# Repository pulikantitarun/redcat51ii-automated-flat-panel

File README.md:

# Universal automated telescope flat panel — Rev C

Rev C is a single-board automated flat-field panel and motorized dust cover. The
included mechanical preset fits the RedCat 51 II, while the parametric CAD supports
other telescope/dew-shield diameters without changing the electronics.

Control options:

- **ASIAIR Plus:** isolated adjustable-output input on J2.
- **ASCOM:** USB-C to the included ASCOM Alpaca CoverCalibrator bridge.
- **Manual:** long-press the onboard or external button.

ASCOM commands receive a renewable 15-second control lease. If the USB bridge stops,
the controller automatically returns to ASIAIR control. USB-C can power the logic for
safe firmware loading, but MAIN 12 V is required for the servo and light panel.

## Rev C improvements

- valid, separately fused input, LED, and servo branches;
- MCU-switched servo rail that defaults off;
- keyed JST-XH servo connector;
- fail-safe normally-closed limit wiring with RC filtering and ESD protection;
- 12 V presence sensing and USB/12 V logic-power ORing;
- native USB-C programming and ASCOM data;
- test pads and UART recovery header;
- filtered ASIAIR input, command hysteresis, 400 ms stability requirement;
- debounced limits, ramped motion, move timeout, fault reporting, NVS calibration;
- LED warm-up/ramp and brightness gamma setting;
- adjustable-diameter CAD, fit gauge, hard-stop tabs, tether eyes, strain relief,
  gasket channel, and Customizer-friendly OpenSCAD clamp.

## Manufacturing set

For turnkey PCB assembly upload:

1. `pcb/Gerbers_RevC.zip`
2. `pcb/BOM.csv`
3. `pcb/PickAndPlace.csv`

Attach `pcb/PCB_Assembly_Top.pdf` and state that both SMT and through-hole parts are
to be assembled. Recommended board order:

- 120 x 75 mm, 4 layers, 1.6 mm FR-4;
- 2 oz finished copper on all layers;
- ENIG, lead-free assembly;
- green solder mask and white silkscreen;
- electrical test, AOI, and assembly inspection photographs;
- turnkey sourcing with no substitutions for U1, U3, U4, L1, L2, Q1/Q3, F1-F3,
  C2, or C7 without approval.

The routed board passes KiCad error-level DRC with **0 errors and 0 unconnected pads**.
All eight supplied STLs are watertight. Silkscreen-only warnings from edge-mounted
connector footprints are recorded separately and do not affect copper fabrication.

## Default RedCat preset

The included STLs use:

- measured scope/dew-shield OD: 80.0 mm;
- 0.8 mm liner per side;
- 0.5 mm diametral print clearance;
- resulting clamp bore: 82.1 mm;
- optical stack diameter: 82 mm.

Do not assume your telescope matches that measurement. Print the short fit gauge
first. See `mechanical/PRESETS.md` for other diameters.

An additional ready-generated **Askar 103 APO starting preset** is included in
`mechanical/presets/Askar-103-APO`. It uses the published 122 mm dew-shield OD,
a 124.1 mm lined clamp bore, and a 125 mm illuminated stack. Measure the actual
shield and print its fit gauge before using the full clamp.

## Release map

- `pcb/` — Gerbers, BOM, centroid, DRC, PDFs, 3D render, STEP, and KiCad source.
- `mechanical/` — STL/STEP parts, CadQuery generator, and OpenSCAD Customizer source.
- `firmware/` — compiled 8 MB ESP32-S3 image and source sketch.
- `ascom/` — tested Windows Alpaca bridge executable and source.
- `docs/INSTALLATION.md` — universal physical installation and wiring.
- `docs/CIRCUIT.md` — circuit blocks, connector map, and GPIO allocation.
- `docs/CONTROL.md` — ASIAIR, ASCOM, manual operation, and USB command protocol.
- `docs/FIRST_ARTICLE_TEST.md` — mandatory electrical, thermal, and optical checks.
- `docs/PCB_ASSEMBLY_ORDER.md` — manufacturer form values and assembly notes.

## Safety and release status

This is a fabrication-ready open-hardware prototype, not a physically qualified
commercial product. DRC, firmware compilation, ASCOM management API, and mesh integrity
were verified digitally. A real first article must still pass the supplied power,
servo-stall, thermal, ASIAIR-output, full-mount-clearance, and illumination-uniformity
tests before unattended use. Always fit the secondary tether.

## License

Hardware, CAD, firmware, bridge software, and documentation are released under
the GNU General Public License v3.0. See `LICENSE` for the full license text.

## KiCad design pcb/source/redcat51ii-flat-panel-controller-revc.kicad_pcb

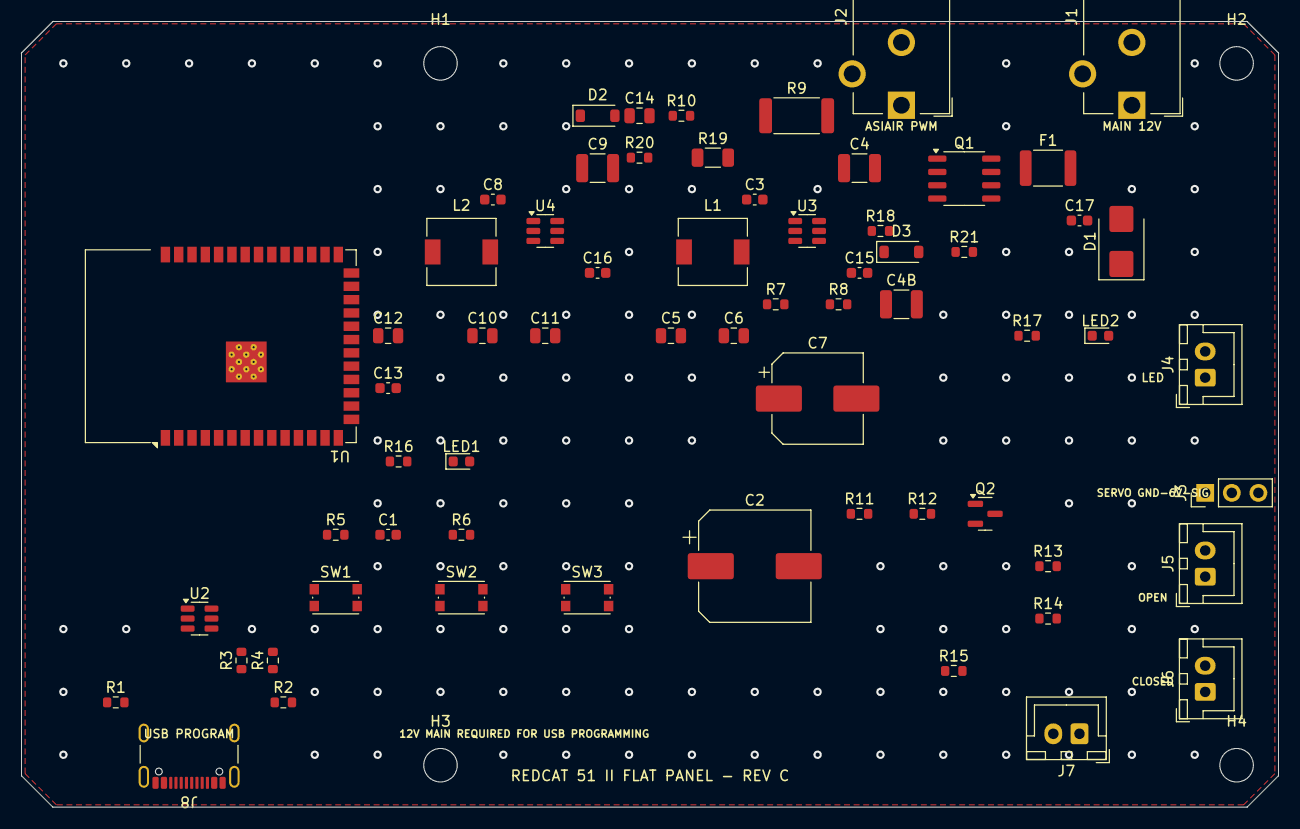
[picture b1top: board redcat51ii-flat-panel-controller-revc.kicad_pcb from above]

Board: 4 copper layers, 120.0 x 75.0 mm, 68 parts (0 on the bottom side), 35 nets, no tracks yet.

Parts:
C1: 1uF; C_0603_1608Metric
C2: 470uF 25V; CP_Elec_10x10.5
C3, C8, C13, C15, C16, C17: 100nF; C_0603_1608Metric
C4, C4B, C9: 10uF 25V; C_1210_3225Metric
C5, C6, C10, C11: 22uF 10V; C_0805_2012Metric
C7: 470uF 10V; CP_Elec_8x10.5
C12, C14: 10uF; C_0805_2012Metric
D1: SMBJ14A; D_SMB
D2: MMSZ5226B 3V3; D_SOD-123
D3: MMSZ5240B 10V; D_SOD-123
F1: 4A 16V PTC; Fuse_1812_4532Metric
H1, H2, H3, H4: M3; MountingHole_3.2mm_M3
J1: MAIN 12V DC5521; BarrelJack_CUI_PJ-102AH_Horizontal
J2: ASIAIR PWM DC5521; BarrelJack_CUI_PJ-102AH_Horizontal
J3: SERVO GND 6V SIG; PinHeader_1x03_P2.54mm_Vertical
J4: LED PANEL; JST_XH_B2B-XH-A_1x02_P2.50mm_Vertical
J5: OPEN LIMIT; JST_XH_B2B-XH-A_1x02_P2.50mm_Vertical
J6: CLOSED LIMIT; JST_XH_B2B-XH-A_1x02_P2.50mm_Vertical
J7: EXT MANUAL; JST_XH_B2B-XH-A_1x02_P2.50mm_Vertical
J8: USB-C PROGRAM; USB_C_Receptacle_GCT_USB4105-xx-A_16P_TopMnt_Horizontal
L1: 3.3uH 6.5A; L_6.3x6.3_H3
L2: 4.7uH 3A; L_6.3x6.3_H3
LED1: STATUS BLUE; LED_0603_1608Metric
LED2: POWER GREEN; LED_0603_1608Metric
Q1: AO4407A; SO-8_3.9x4.9mm_P1.27mm
Q2: AO3400A; SOT-23
R1, R2: 5.1k; R_0603_1608Metric
R3, R4: 22R; R_0603_1608Metric
R5, R6, R10, R12, R13, R14, R15: 10k; R_0603_1608Metric
R7: 64.9k 1%; R_0603_1608Metric
R8: 10k 1%; R_0603_1608Metric
R9: 470R 1W; R_2512_6332Metric
R11: 100R; R_0603_1608Metric
R16, R17: 1k; R_0603_1608Metric
R18, R21: 100k; R_0603_1608Metric
R19: 0R; R_1206_3216Metric
R20: 3k3; R_0603_1608Metric
SW1: RESET; SW_Push_1P1T_NO_CK_KMR2
SW2: BOOT; SW_Push_1P1T_NO_CK_KMR2
SW3: MANUAL; SW_Push_1P1T_NO_CK_KMR2
U1: ESP32-S3-WROOM-1-N8R8; ESP32-S3-WROOM-1
U2: USBLC6-2SC6; SOT-23-6
U3: AP62401WU-7; TSOT-23-6
U4: AP63203WU-7; TSOT-23-6

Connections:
+3V3: C10.1, C11.1, C12.1, C13.1, L2.2, R5.1, R6.1, R13.1, R14.1, R15.1, R17.1, U1.2, U4.4
+6V: C5.1, C6.1, C7.1, J3.2, L1.2, R7.1
+12V: C2.1, C4.1, C4B.1, C9.1, C15.1, C16.1, D1.1, D3.1, J4.1, Q1.1, Q1.2, Q1.3, R18.1, U3.3, U4.3, U4.5
+12V_FUSED: F1.2, Q1.5, Q1.6, Q1.7, Q1.8
+12V_RAW: C17.1, F1.1, J1.1
ASIAIR+: J2.1, R9.1, R10.1
ASIAIR-: J2.2, J2.3, R9.2, R19.1
ASIAIR_SIG: C14.1, D2.1, R10.2, R20.1, U1.4
BOOT: R6.2, SW2.1, U1.27
BST3: C8.1, U4.6
BST6: C3.1, U3.6
BUTTON_SIG: J7.1, R15.2, SW3.1, U1.17
CC1: J8.A5, R1.1
CC2: J8.B5, R2.1
CLOSED_SIG: J6.1, R14.2, U1.7
EN: C1.1, R5.2, SW1.1, U1.3
EN6: R18.2, U3.5
FB6: R7.2, R8.1, U3.4
GATE12: D3.2, Q1.4, R21.1
GND: C1.2, C2.2, C4.2, C4B.2, C5.2, C6.2, C7.2, C9.2, C10.2, C11.2, C12.2, C13.2, C14.2, C15.2, C16.2, C17.2, D1.2, D2.2, J1.2, J1.3, J3.1, J5.2, J6.2, J7.2, J8.A1, J8.A12, J8.B1, J8.B12, J8.S1, LED1.1, LED2.1, Q2.2, R1.2, R2.2, R8.2, R12.2, R19.2, R20.2, R21.2, SW1.2, SW2.2, SW3.2, U1.1, U1.40, U1.41, U2.2, U3.1, U4.1
LED_GATE: Q2.1, R11.2, R12.1
LED_NEG: J4.2, Q2.3
LED_PWM: R11.1, U1.5
OPEN_SIG: J5.1, R13.2, U1.6
PWR_LED: LED2.2, R17.2
SERVO_SIG: J3.3, U1.11
STATUS_A: LED1.2, R16.2
STATUS_LED: R16.1, U1.8
SW3: C8.2, L2.1, U4.2
SW6: C3.2, L1.1, U3.2
USB_D+: R3.2, U1.14
USB_D+_J: J8.A6, J8.B6, R3.1, U2.1, U2.6
USB_D-: R4.2, U1.13
USB_D-_J: J8.A7, J8.B7, R4.1, U2.3, U2.4
USB_VBUS: J8.A4, J8.A9, J8.B4, J8.B9, U2.5

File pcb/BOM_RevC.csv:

Comment,Designator,Footprint,Quantity
1uF,C1,C_0603_1608Metric,1
470uF 25V,C2,CP_Elec_10x10.5,1
100nF,"C3,C8,C13,C15,C16,C17",C_0603_1608Metric,6
10uF 25V,"C4B,C4,C9",C_1210_3225Metric,3
22uF 10V,"C5,C6,C10,C11",C_0805_2012Metric,4
470uF 10V,C7,CP_Elec_8x10.5,1
10uF,"C12,C14",C_0805_2012Metric,2
SMBJ14A,D1,D_SMB,1
MMSZ5226B 3V3,D2,D_SOD-123,1
MMSZ5240B 10V,D3,D_SOD-123,1
4A 16V PTC,F1,Fuse_1812_4532Metric,1
MAIN 12V DC5521,J1,BarrelJack_CUI_PJ-102AH_Horizontal,1
ASIAIR PWM DC5521,J2,BarrelJack_CUI_PJ-102AH_Horizontal,1
SERVO GND 6V SIG,J3,PinHeader_1x03_P2.54mm_Vertical,1
LED PANEL,J4,JST_XH_B2B-XH-A_1x02_P2.50mm_Vertical,1
OPEN LIMIT,J5,JST_XH_B2B-XH-A_1x02_P2.50mm_Vertical,1
CLOSED LIMIT,J6,JST_XH_B2B-XH-A_1x02_P2.50mm_Vertical,1
EXT MANUAL,J7,JST_XH_B2B-XH-A_1x02_P2.50mm_Vertical,1
USB-C PROGRAM,J8,USB_C_Receptacle_GCT_USB4105-xx-A_16P_TopMnt_Horizontal,1
3.3uH 6.5A,L1,L_6.3x6.3_H3,1
4.7uH 3A,L2,L_6.3x6.3_H3,1
STATUS BLUE,LED1,LED_0603_1608Metric,1
POWER GREEN,LED2,LED_0603_1608Metric,1
AO4407A,Q1,SO-8_3.9x4.9mm_P1.27mm,1
AO3400A,Q2,SOT-23,1
5.1k,"R1,R2",R_0603_1608Metric,2
22R,"R3,R4",R_0603_1608Metric,2
10k,"R5,R6,R10,R12,R13,R14,R15",R_0603_1608Metric,7
64.9k 1%,R7,R_0603_1608Metric,1
10k 1%,R8,R_0603_1608Metric,1
470R 1W,R9,R_2512_6332Metric,1
100R,R11,R_0603_1608Metric,1
1k,"R16,R17",R_0603_1608Metric,2
100k,"R18,R21",R_0603_1608Metric,2
0R,R19,R_1206_3216Metric,1
3k3,R20,R_0603_1608Metric,1
RESET,SW1,SW_Push_1P1T_NO_CK_KMR2,1
BOOT,SW2,SW_Push_1P1T_NO_CK_KMR2,1
MANUAL,SW3,SW_Push_1P1T_NO_CK_KMR2,1
ESP32-S3-WROOM-1-N8R8,U1,ESP32-S3-WROOM-1,1
USBLC6-2SC6,U2,SOT-23-6,1
AP62401WU-7,U3,TSOT-23-6,1
AP63203WU-7,U4,TSOT-23-6,1

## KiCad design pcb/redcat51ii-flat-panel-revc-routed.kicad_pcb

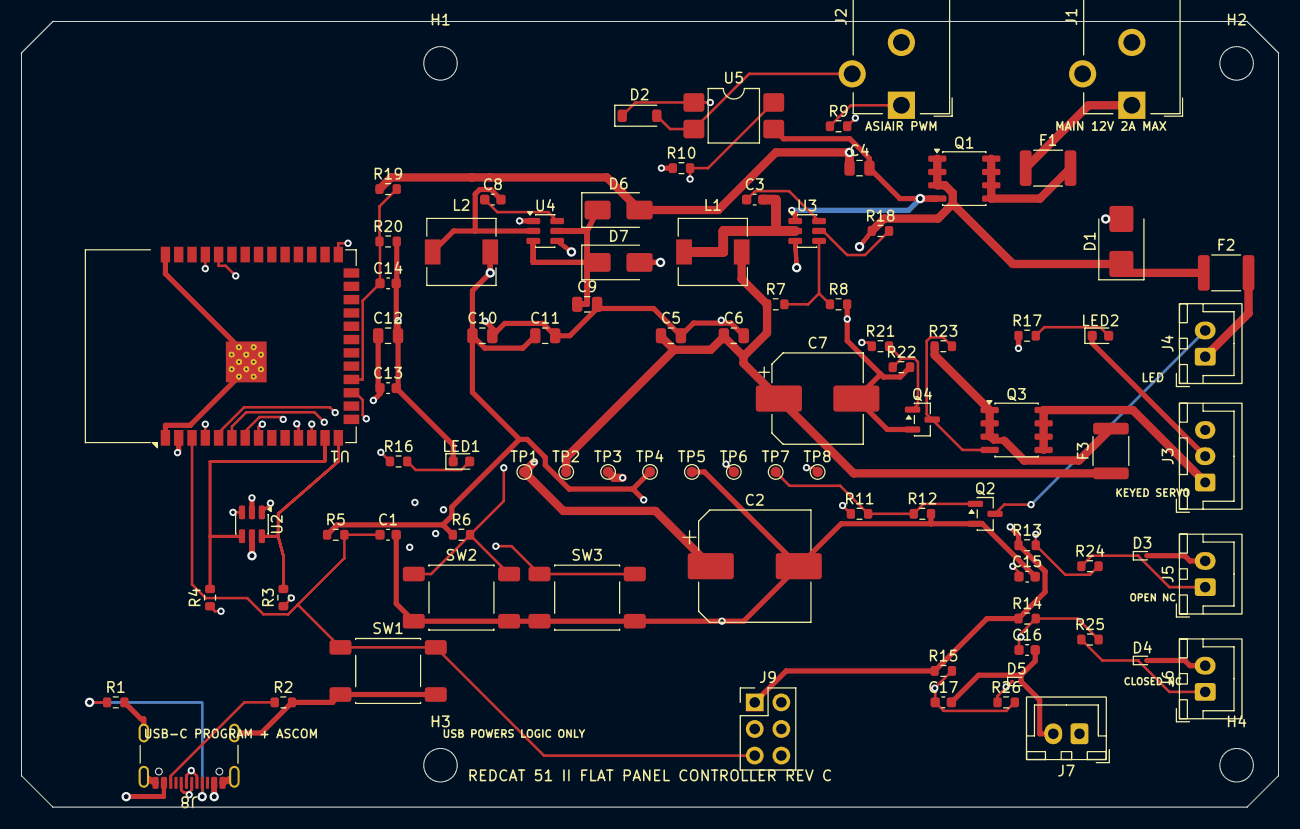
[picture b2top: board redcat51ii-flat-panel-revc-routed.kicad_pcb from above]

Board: 4 copper layers, 120.0 x 75.0 mm, 90 parts (0 on the bottom side), 48 nets.

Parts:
C1: 1uF; C_0603_1608Metric
C2: 470uF 25V; CP_Elec_10x10.5
C3, C8, C13, C14, C15, C16, C17: 100nF; C_0603_1608Metric
C4, C9: 10uF 25V; C_0805_2012Metric
C5, C6, C10, C11: 22uF 10V; C_0805_2012Metric
C7: 470uF 10V; CP_Elec_8x10.5
C12: 10uF; C_0805_2012Metric
D1: SMBJ18A; D_SMB
D2: 1N4148W; D_SOD-123
D3, D4, D5: ESD9B3.3ST5G; D_SOD-923
D6: SS14 12V LOGIC OR; D_SMA
D7: SS14 USB LOGIC OR; D_SMA
F1: MF-MSMF200/16X 2A 16V PTC; Fuse_1812_4532Metric
F2: MF-MSMF110/16X LED 1.1A; Fuse_1812_4532Metric
F3: MF-MSMF260/8X SERVO 2.6A; Fuse_1812_4532Metric
H1, H2, H3, H4: M3; MountingHole_3.2mm_M3
J1: MAIN 12V DC5521; BarrelJack_CUI_PJ-102AH_Horizontal
J2: ASIAIR PWM DC5521; BarrelJack_CUI_PJ-102AH_Horizontal
J3: KEYED SERVO 6V GND SIG; JST_XH_B3B-XH-A_1x03_P2.50mm_Vertical
J4: LED PANEL; JST_XH_B2B-XH-A_1x02_P2.50mm_Vertical
J5: OPEN LIMIT NC; JST_XH_B2B-XH-A_1x02_P2.50mm_Vertical
J6: CLOSED LIMIT NC; JST_XH_B2B-XH-A_1x02_P2.50mm_Vertical
J7: EXT MANUAL; JST_XH_B2B-XH-A_1x02_P2.50mm_Vertical
J8: USB-C PROGRAM; USB_C_Receptacle_GCT_USB4105-xx-A_16P_TopMnt_Horizontal
J9: UART RECOVERY; PinHeader_2x03_P2.54mm_Vertical
L1: 3.3uH 6.5A; L_6.3x6.3_H3
L2: 4.7uH 3A; L_6.3x6.3_H3
LED1: STATUS BLUE; LED_0603_1608Metric
LED2: POWER GREEN; LED_0603_1608Metric
Q1: AO4407A; SO-8_3.9x4.9mm_P1.27mm
Q2: AO3400A; SOT-23
Q3: AO4407A SERVO SWITCH; SO-8_3.9x4.9mm_P1.27mm
Q4: MMBT3904; SOT-23
R1, R2: 5.1k; R_0603_1608Metric
R3, R4: 22R; R_0603_1608Metric
R5, R6, R10, R12, R13, R14, R15: 10k; R_0603_1608Metric
R7: 64.9k 1%; R_0603_1608Metric
R8: 10k 1%; R_0603_1608Metric
R9: 2.2k; R_0603_1608Metric
R11: 100R; R_0603_1608Metric
R16, R17, R24, R25, R26: 1k; R_0603_1608Metric
R18, R19, R22, R23: 100k; R_0603_1608Metric
R20: 22k; R_0603_1608Metric
R21: 4.7k; R_0603_1608Metric
SW1: RESET; SW_Push_1P1T_NO_E-Switch_TL3301NxxxxxG
SW2: BOOT; SW_Push_1P1T_NO_E-Switch_TL3301NxxxxxG
SW3: MANUAL; SW_Push_1P1T_NO_E-Switch_TL3301NxxxxxG
TP1: 12V; TestPoint_Pad_D1.0mm
TP2: 6V; TestPoint_Pad_D1.0mm
TP3: 6V_SW; TestPoint_Pad_D1.0mm
TP4: 3V3; TestPoint_Pad_D1.0mm
TP5: GND; TestPoint_Pad_D1.0mm
TP6: ASIAIR; TestPoint_Pad_D1.0mm
TP7: LED_GATE; TestPoint_Pad_D1.0mm
TP8: SERVO_SIG; TestPoint_Pad_D1.0mm
U1: ESP32-S3-WROOM-1-N8; ESP32-S3-WROOM-1
U2: USBLC6-2SC6; SOT-23-6
U3: AP62401WU-7; TSOT-23-6
U4: AP63203WU-7; TSOT-23-6
U5: LTV-817S; SMDIP-4_W7.62mm

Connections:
+3V3: C10.1, C11.1, C12.1, C13.1, J9.1, L2.2, R5.1, R6.1, R10.1, R13.1, R14.1, R15.1, R17.1, TP4.1, U1.2, U4.4
+6V: C5.1, C6.1, C7.1, F3.1, L1.2, R7.1, TP2.1
+6V_FUSED: F3.2, Q3.1, Q3.2, Q3.3, R23.1
+6V_SERVO: J3.1, Q3.5, Q3.6, Q3.7, Q3.8, TP3.1
+12V: C2.1, C4.1, D1.1, D6.2, F2.1, Q1.1, Q1.2, Q1.3, R18.1, R19.1, TP1.1, U3.3
+12V_FUSED: F1.2, Q1.5, Q1.6, Q1.7, Q1.8
+12V_LED: F2.2, J4.1
+12V_RAW: F1.1, J1.1
ASIAIR+: J2.1, R9.1
ASIAIR-: D2.2, J2.2, J2.3, U5.2
ASIAIR_LED: D2.1, R9.2, U5.1
ASIAIR_SIG: R10.2, TP6.1, U1.4, U5.4
BOOT: J9.6, R6.2, SW2.1, U1.27
BST3: C8.1, U4.6
BST6: C3.1, U3.6
BUTTON_RAW: D5.1, J7.1, R26.1
BUTTON_SIG: C17.1, R15.2, R26.2, SW3.1, U1.17
CC1: J8.A5, R1.1
CC2: J8.B5, R2.1
CLOSED_RAW: D4.1, J6.1, R25.1
CLOSED_SIG: C16.1, R14.2, R25.2, U1.7
EN: C1.1, J9.5, R5.2, SW1.1, U1.3
EN6: R18.2, U3.5
FB6: R7.2, R8.1, U3.4
GND: C1.2, C2.2, C4.2, C5.2, C6.2, C7.2, C9.2, C10.2, C11.2, C12.2, C13.2, C14.2, C15.2, C16.2, C17.2, D1.2, D3.2, D4.2, D5.2, J1.2, J1.3, J3.2, J5.2, J6.2, J7.2, J8.A1, J8.A12, J8.B1, J8.B12, J8.SH, J9.2, LED1.1, LED2.1, Q1.4, Q2.2, Q4.2, R1.2, R2.2, R8.2, R12.2, R20.2, R22.2, SW1.2, SW2.2, SW3.2, TP5.1, U1.1, U1.40, U1.41, U2.2, U3.1, U4.1, U5.3
LED_GATE: Q2.1, R11.2, R12.1, TP7.1
LED_NEG: J4.2, Q2.3
LED_PWM: R11.1, U1.5
LOGIC_VIN: C9.1, D6.1, D7.1, U4.3, U4.5
OPEN_RAW: D3.1, J5.1, R24.1
OPEN_SIG: C15.1, R13.2, R24.2, U1.6
PWR_LED: LED2.2, R17.2
PWR_SENSE: C14.1, R19.2, R20.1, U1.18
SERVO_BASE: Q4.1, R21.2, R22.1
SERVO_GATE: Q3.4, Q4.3, R23.2
SERVO_PWR_EN: R21.1, U1.12
SERVO_SIG: J3.3, TP8.1, U1.11
STATUS_A: LED1.2, R16.2
STATUS_LED: R16.1, U1.8
SW3: C8.2, L2.1, U4.2
SW6: C3.2, L1.1, U3.2
UART_RX: J9.4, U1.36
UART_TX: J9.3, U1.37
USB_D+: R3.2, U1.14, U2.6
USB_D+_J: J8.A6, J8.B6, R3.1, U2.1
USB_D-: R4.2, U1.13, U2.4
USB_D-_J: J8.A7, J8.B7, R4.1, U2.3
USB_VBUS: D7.2, J8.A4, J8.A9, J8.B4, J8.B9, U2.5

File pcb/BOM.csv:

Item,Designator,Qty,Manufacturer,Manufacturer Part Number,Description,Package,Assembly Notes
1,U1,1,Espressif,ESP32-S3-WROOM-1-N8,ESP32-S3 module 8MB flash,ESP32-S3-WROOM-1,Antenna end at board edge; no PSRAM required
2,U2,1,STMicroelectronics,USBLC6-2SC6,USB 2-line ESD protector,SOT-23-6,
3,U3,1,Diodes Incorporated,AP62401WU-7,4A forced-PWM synchronous buck,TSOT-23-6,
4,U4,1,Diodes Incorporated,AP63203WU-7,3.3V 2A synchronous buck,TSOT-23-6,
5,U5,1,Lite-On,LTV-817S-TA1,Optocoupler,SMDIP-4 W7.62,
6,Q1 Q3,2,Alpha & Omega Semiconductor,AO4407A,P-channel MOSFET reverse protection / servo switch,SO-8,
7,Q2,1,Alpha & Omega Semiconductor,AO3400A,N-channel LED MOSFET,SOT-23,
8,Q4,1,onsemi,MMBT3904LT1G,NPN servo-gate driver,SOT-23,
9,D1,1,Littelfuse,SMBJ18A,18V unidirectional TVS diode,SMB,Observe cathode mark
10,D2,1,Diodes Incorporated,1N4148W-7-F,Optocoupler reverse clamp,SOD-123,Observe cathode mark
11,D3 D4 D5,3,onsemi,ESD9B3.3ST5G,3.3V bidirectional ESD protection,SOD-923,
12,D6 D7,2,Diodes Incorporated,SS14-13-F,1A 40V Schottky power OR diode,SMA,Observe cathode mark
13,F1,1,Bourns,MF-MSMF200/16X-2,2.0A hold 16V resettable input fuse,1812,System continuous input rating is 2A
14,F2,1,Bourns,MF-MSMF110/16X-2,1.1A hold 16V resettable LED fuse,1812,
15,F3,1,Bourns,MF-MSMF260/8X-2,2.6A hold 8V resettable servo fuse,1812,
16,L1,1,Coilcraft,XAL6060-332MEB,3.3uH shielded inductor 6.5A,6x6mm,
17,L2,1,Bourns,SRN6045TA-4R7M,4.7uH shielded inductor,6x6mm,Confirm pad compatibility during DFM
18,C2,1,Panasonic,EEE-FK1E471P,470uF 25V low-ESR capacitor,10x10.2mm,Observe polarity
19,C7,1,Panasonic,EEE-FK1A471P,470uF 10V low-ESR capacitor,8x10.2mm,Observe polarity
20,C4 C9,2,Murata,GRM21BR61E106KA73L,10uF 25V X5R,0805,
21,C5 C6 C10 C11,4,Murata,GRM21BR61A226ME44L,22uF 10V X5R,0805,
22,C12,1,Murata,GRM21BR61A106KE19L,10uF 10V X5R,0805,
23,C1,1,Murata,GRM188R61A105KA61D,1uF 10V X5R,0603,
24,C3 C8 C13 C14 C15 C16 C17,7,Murata,GRM188R71C104KA01D,100nF 16V X7R,0603,
25,R1 R2,2,Yageo,RC0603FR-075K1L,5.1k 1%,0603,
26,R3 R4,2,Yageo,RC0603FR-0722RL,22R 1%,0603,
27,R5 R6 R8 R10 R12 R13 R14 R15,8,Yageo,RC0603FR-0710KL,10k 1%,0603,
28,R7,1,Yageo,RC0603FR-0764K9L,64.9k 1%,0603,
29,R9,1,Yageo,RC0603FR-072K2L,2.2k 1%,0603,
30,R11,1,Yageo,RC0603FR-07100RL,100R 1%,0603,
31,R16 R17 R24 R25 R26,5,Yageo,RC0603FR-071KL,1k 1%,0603,
32,R18 R19 R22 R23,4,Yageo,RC0603FR-07100KL,100k 1%,0603,
33,R20,1,Yageo,RC0603FR-0722KL,22k 1%,0603,
34,R21,1,Yageo,RC0603FR-074K7L,4.7k 1%,0603,
35,LED1,1,Lite-On,LTST-C190TBKT,Blue status LED,0603,Observe polarity
36,LED2,1,Lite-On,LTST-C190KGKT,Green power LED,0603,Observe polarity
37,SW1 SW2 SW3,3,E-Switch,TL3301NF160QG,Tactile switch,SMD 6x6mm,
38,J8,1,GCT,USB4105-GF-A,USB-C USB2 receptacle,16-pin hybrid,Hybrid SMT/THT
39,J1 J2,2,Same Sky,PJ-102AH,DC barrel jack 2.5A,THT horizontal,Hybrid assembly; MAIN is fused to 2A continuous
40,J4 J5 J6 J7,4,JST,B2B-XH-A(LF)(SN),2-pin keyed header 2.50mm,THT,Hybrid assembly
41,J3,1,JST,B3B-XH-A(LF)(SN),3-pin keyed servo header 2.50mm,THT,Pin 1 6V; pin 2 GND; pin 3 signal
42,J9,1,Samtec,TSW-103-07-G-D,2x3 UART recovery header 2.54mm,THT,Optional service connector
43,TP1 TP2 TP3 TP4 TP5 TP6 TP7 TP8,8,Generic,DNP,1mm test pad,DNP,No component fitted
